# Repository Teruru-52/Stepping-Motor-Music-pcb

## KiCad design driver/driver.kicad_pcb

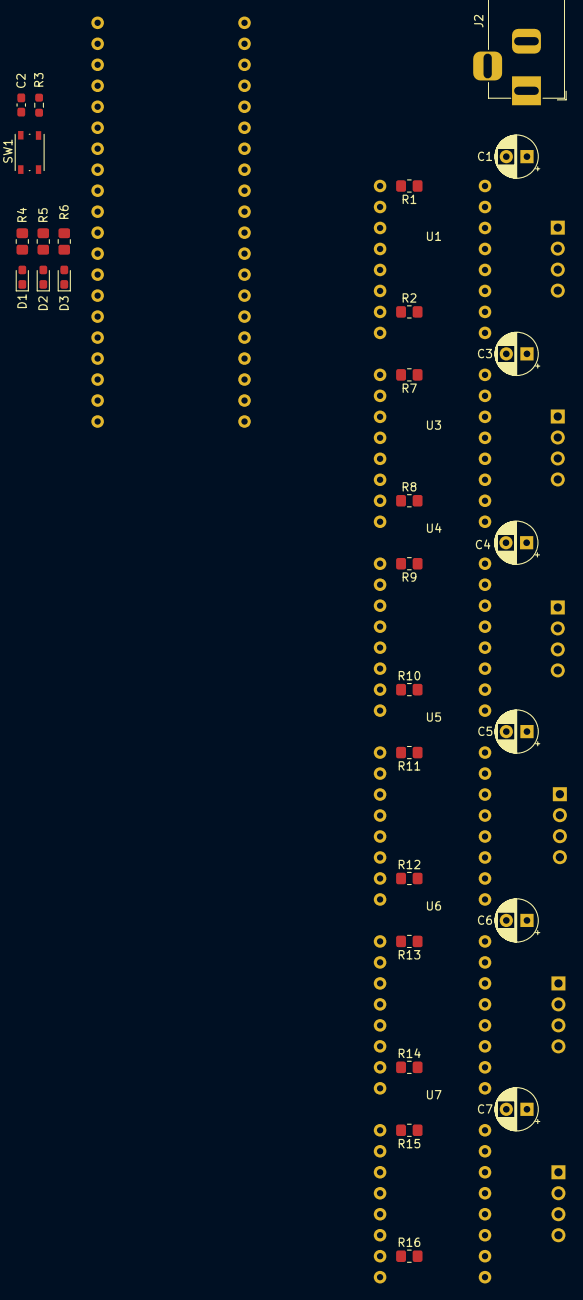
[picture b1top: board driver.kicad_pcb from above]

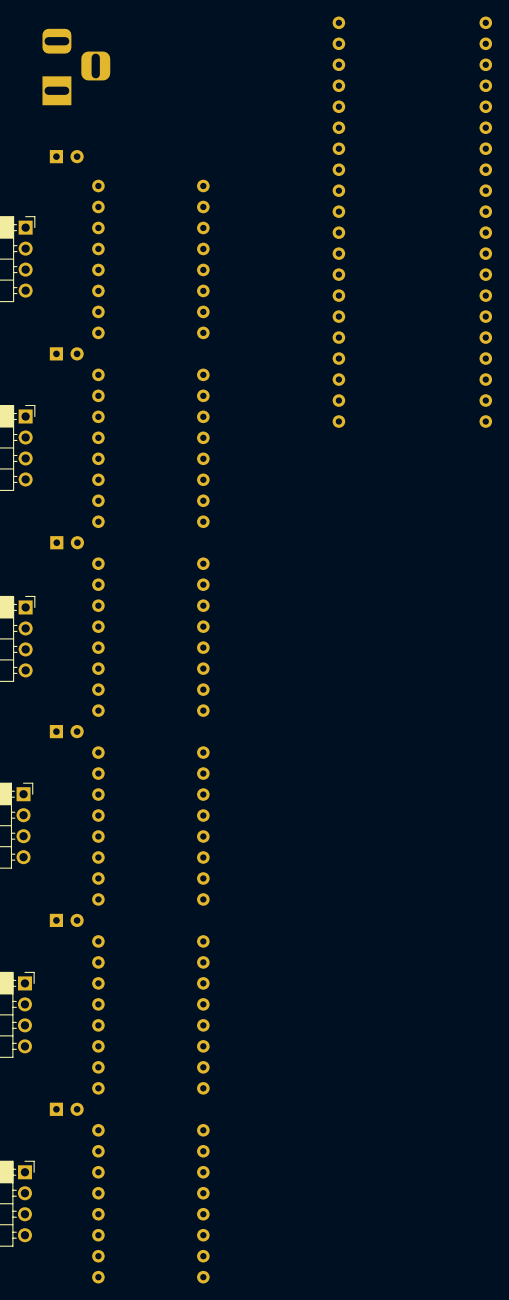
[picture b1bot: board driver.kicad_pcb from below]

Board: 2 copper layers, 41 parts (6 on the bottom side), 56 nets, no tracks yet.

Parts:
C1, C3, C4, C5, C6, C7: 10u; CP_Radial_D5.0mm_P2.50mm
C2: 0.1u; C_0603_1608Metric_Pad1.08x0.95mm_HandSolder
D1, D2, D3: LED; LED_0603_1608Metric_Pad1.05x0.95mm_HandSolder
J1, J3, J4, J5, J6, J7: Conn_01x04_Female; PinSocket_1x04_P2.54mm_Horizontal
J2: Barrel_Jack; BarrelJack_Horizontal
R1, R2, R7, R8, R9, R10, R11, R12, R13, R14, R15, R16: 10k; R_0805_2012Metric_Pad1.20x1.40mm_HandSolder
R3: 10k; R_0603_1608Metric_Pad0.98x0.95mm_HandSolder
R4, R5, R6: 1k; R_0805_2012Metric_Pad1.20x1.40mm_HandSolder
SW1: SKRPACE; SW_Push_1P1T_NO_Vertical_Wuerth_434133025816
U1, U3, U4, U5, U6, U7: a4988
U2: RaspberryPi Pico; raspberrypi_pico

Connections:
+3.3V: R1.1, R3.1, R7.1, R9.1, R11.1, R13.1, R15.1, U1.15 (VDD), U2.36 (3V3_OUT), U3.15 (VDD), U4.15 (VDD), U5.15 (VDD), U6.15 (VDD), U7.15 (VDD)
+BATT: C1.1, C3.1, C4.1, C5.1, C6.1, C7.1, J2.1, U1.9 (VMOT), U3.9 (VMOT), U4.9 (VMOT), U5.9 (VMOT), U6.9 (VMOT), U7.9 (VMOT)
/MicroController/DIR: U1.8 (DIR), U2.12 (UART1_RX/I2C1_SCL/SPI1_CSn/GP9), U3.8 (DIR), U4.8 (DIR), U5.8 (DIR), U6.8 (DIR), U7.8 (DIR)
/MicroController/ENABLE1: R1.2, U1.1 (ENABLE), U2.34 (GP28/ADC2)
/MicroController/ENABLE2: R7.2, U2.31 (GP26/ADC0/I2C1_SDA), U3.1 (ENABLE)
/MicroController/ENABLE3: R9.2, U2.27 (GP21/I2C0_SCL), U4.1 (ENABLE)
/MicroController/ENABLE4: R11.2, U2.25 (GP19/SPI0_TX/I2C1_SCL), U5.1 (ENABLE)
/MicroController/ENABLE5: R13.2, U2.17 (UART0_RX/I2C0_SCL/SPI1_CSn/GP13), U6.1 (ENABLE)
/MicroController/ENABLE6: R15.2, U2.15 (I2C1_SCL/SPI1_TX/GP11), U7.1 (ENABLE)
/MicroController/MS1: U1.2 (MS1), U2.4 (I2C1_SDA/SPI0_SCK/GP2), U3.2 (MS1), U4.2 (MS1), U5.2 (MS1), U6.2 (MS1), U7.2 (MS1)
/MicroController/MS2: U1.3 (MS2), U2.5 (I2C1_SCL/SPI0_TX/GP3), U3.3 (MS2), U4.3 (MS2), U5.3 (MS2), U6.3 (MS2), U7.3 (MS2)
/MicroController/MS3: U1.4 (MS3), U2.9 (I2C1_SDA/SPI0_SCK/GP6), U3.4 (MS3), U4.4 (MS3), U5.4 (MS3), U6.4 (MS3), U7.4 (MS3)
/MicroController/PMW3: R10.1, U2.26 (GP20/I2C0_SDA), U4.7 (STEP)
/MicroController/PWM1: R2.1, U1.7 (STEP), U2.32 (GP27/ADC1/I2C1_SCL)
/MicroController/PWM2: R8.1, U2.29 (GP22), U3.7 (STEP)
/MicroController/PWM4: R12.1, U2.24 (GP18/SPI0_SCK/I2C1_SDA), U5.7 (STEP)
/MicroController/PWM5: R14.1, U2.16 (UART0_TX/I2C0_SDA/SPI1_RX/GP12), U6.7 (STEP)
/MicroController/PWM6: R16.1, U2.14 (I2C1_SDA/SPI1_SCK/GP10), U7.7 (STEP)
GND: C1.2, C2.2, C3.2, C4.2, C5.2, C6.2, C7.2, D1.1 (K), D2.1 (K), D3.1 (K), J2.2, R2.2, R8.2, R10.2, R12.2, R14.2, R16.2, SW1.1, U1.10 (GND), U1.16 (GND), U2.3 (GND), U2.8 (GND), U2.13 (GND), U2.18 (GND), U2.23 (GND), U2.28 (GND), U2.33 (GND/AGND), U2.38 (GND), U3.10 (GND), U3.16 (GND), U4.10 (GND), U4.16 (GND), U5.10 (GND), U5.16 (GND), U6.10 (GND), U6.16 (GND), U7.10 (GND), U7.16 (GND)
unnamed: C2.1, R3.2, SW1.2, U2.6 (UART1_TX/I2C0_SDA/SPI0_RX/GP4)
unnamed: D1.2 (A), R4.2
unnamed: D2.2 (A), R5.2
unnamed: D3.2 (A), R6.2
unnamed: J1.1, U1.11 (B2)
unnamed: J1.2, U1.12 (A2)
unnamed: J1.3, U1.13 (B1)
unnamed: J1.4, U1.14 (A1)
unnamed: J3.1, U3.11 (B2)
unnamed: J3.2, U3.12 (A2)
unnamed: J3.3, U3.13 (B1)
unnamed: J3.4, U3.14 (A1)
unnamed: J4.1, U4.11 (B2)
unnamed: J4.2, U4.12 (A2)
unnamed: J4.3, U4.13 (B1)
unnamed: J4.4, U4.14 (A1)
unnamed: J5.1, U5.11 (B2)
unnamed: J5.2, U5.12 (A2)
unnamed: J5.3, U5.13 (B1)
unnamed: J5.4, U5.14 (A1)
unnamed: J6.1, U6.11 (B2)
unnamed: J6.2, U6.12 (A2)
unnamed: J6.3, U6.13 (B1)
unnamed: J6.4, U6.14 (A1)
unnamed: J7.1, U7.11 (B2)
unnamed: J7.2, U7.12 (A2)
unnamed: J7.3, U7.13 (B1)
unnamed: J7.4, U7.14 (A1)
unnamed: R4.1, U2.7 (UART1_RX/I2C0_SCL/SPI0_SCn/GP5)
unnamed: R5.1, U2.10 (I2C1_SCL/SPI0_TX/GP7)
unnamed: R6.1, U2.11 (UART1_TX/I2C1_SDA/SPI0_RX/GP8)
unnamed: U1.5 (RESET), U1.6 (SLEEP)
unnamed: U3.5 (RESET), U3.6 (SLEEP)
unnamed: U4.5 (RESET), U4.6 (SLEEP)
unnamed: U5.5 (RESET), U5.6 (SLEEP)
unnamed: U6.5 (RESET), U6.6 (SLEEP)
unnamed: U7.5 (RESET), U7.6 (SLEEP)

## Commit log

2022-12-20 add circuit
2023-02-18 部品配置完了
2023-02-18 pcb作成完了
